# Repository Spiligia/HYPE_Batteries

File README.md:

**Boston University EC 463 & 464 Senior Design Project**

Members: Spencer Piligian, Ismaeel AlAlawi, Steven Wang, Yusheng Chen and Daniel Kao

## Welcome to Team 23: HYP Batteries! 

Our hybrid-chemistry battery pack design aims to fill niche market gap in high performance battery pack for small aircraft by combining two batteries with two different discharge characteristics. These two cell chemistries can achieve a variable-max discharge rate, allowing us to design a smaller battery pack while also fulfilling power requirements during the launch. This pack setup will help eGliders achieve a safe flight through the use of electric power and as a result, will minimize the risk of mechanical failure for our client’s conventional mechanical engines, whose vibration causes other parts of the aircraft to wear out and ultimately increases the chance of failure.

Link to google drive for more information / process development 

https://drive.google.com/drive/u/0/folders/0AN8LmBJzQ7HJUk9PVA

For member access please email: spiligia@bu.edu

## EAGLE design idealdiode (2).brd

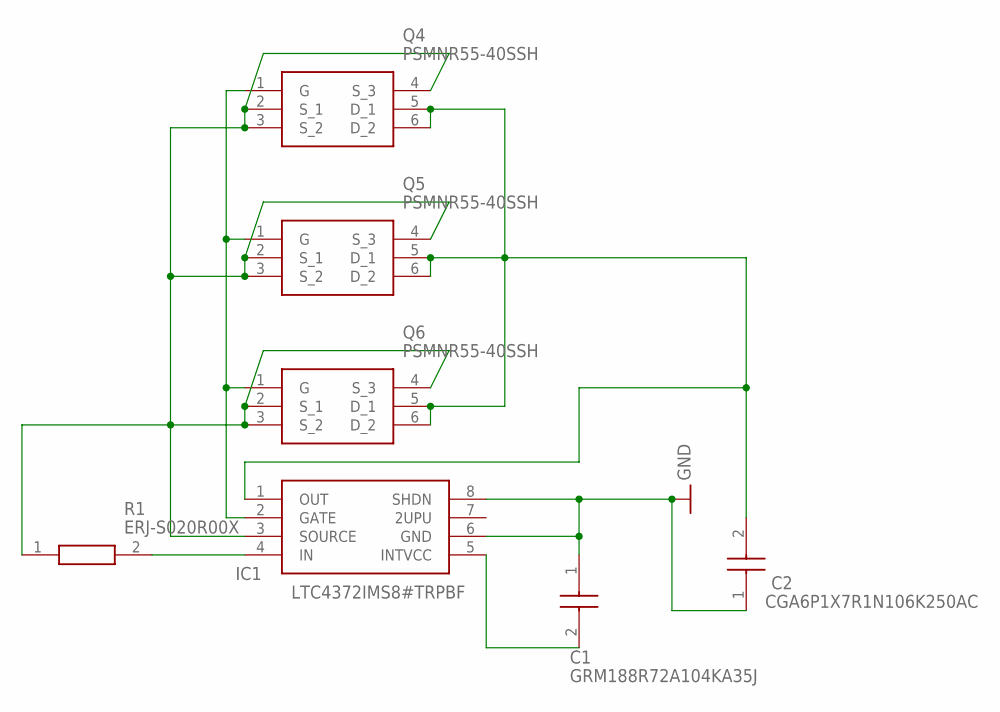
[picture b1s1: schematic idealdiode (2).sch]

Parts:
C1: GRM188R72A104KA35J; CAPC1608X90N
C2: CGA6P1X7R1N106K250AC; CAPC3225X280N
IC1: LTC4372IMS8#TRPBF; SOP65P490X110-8N
Q4, Q5, Q6: PSMNR55-40SSH; PSMNR5540SSH
R1: ERJ-S020R00X; ERJS02_U02_(0402)

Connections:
GND: C1.1, C2.1, IC1.6 (GND), IC1.8 (SHDN)
unnamed: IC1.2 (GATE), Q4.1 (G), Q5.1 (G), Q6.1 (G)
unnamed: IC1.3 (SOURCE), Q4.2 (S_1), Q4.3 (S_2), Q4.4 (S_3), Q5.2 (S_1), Q5.3 (S_2), Q5.4 (S_3), Q6.2 (S_1), Q6.3 (S_2), Q6.4 (S_3), R1.1
unnamed: C2.2, IC1.1 (OUT), Q4.5 (D_1), Q4.6 (D_2), Q5.5 (D_1), Q5.6 (D_2), Q6.5 (D_1), Q6.6 (D_2)
unnamed: C1.2, IC1.5 (INTVCC)
unnamed: IC1.4 (IN), R1.2

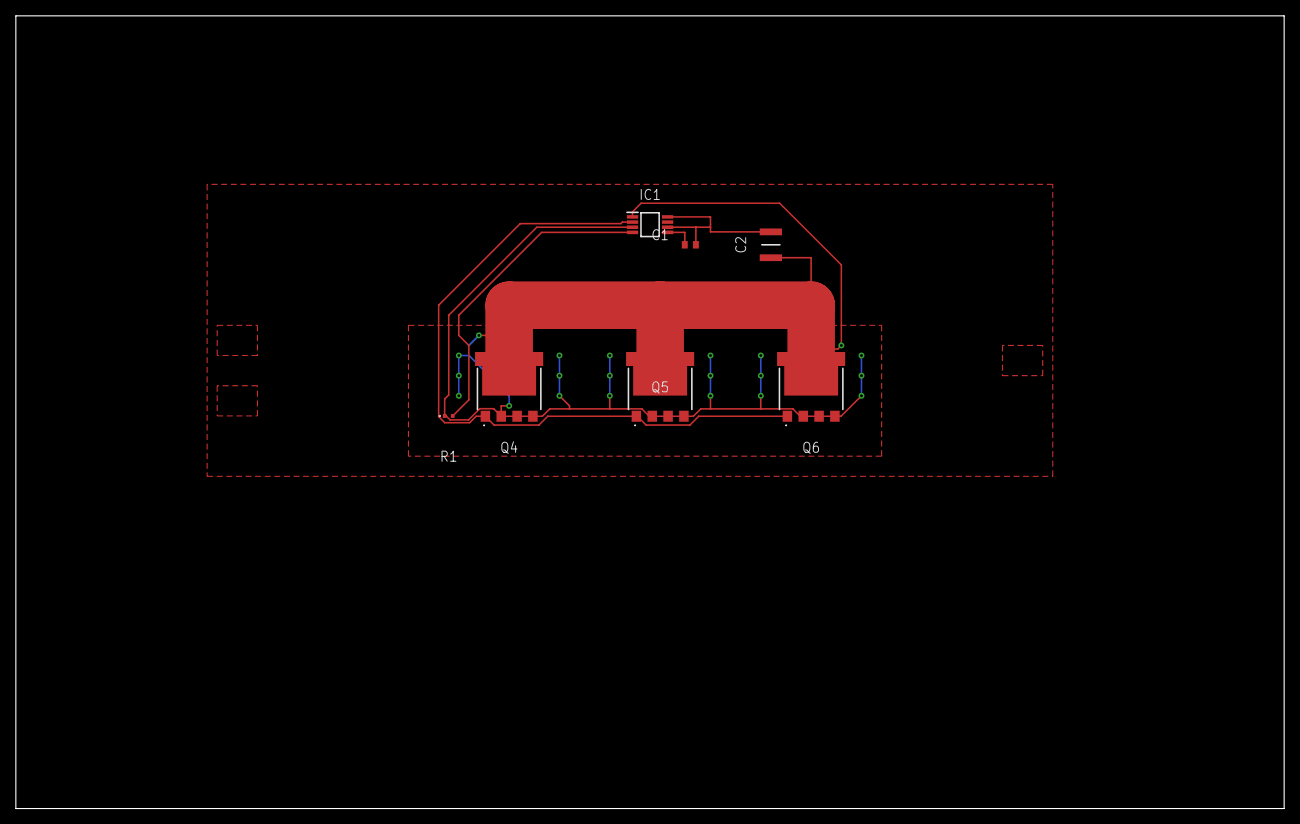
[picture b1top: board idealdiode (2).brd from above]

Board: 2 copper layers, 160.0 x 100.0 mm, 7 parts (0 on the bottom side), 6 nets.

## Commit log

2022-01-26 Code for temp control
    Using an arduino BLE
2022-01-26 udpate name
2022-01-26 .ino ext added
2022-01-27 updated some values for base arduino
    1023bit for non ble arduinos - may use megas
2022-02-01 output update
    set output text to serial monitor if over temp
2022-04-15 Renders of Thermistor cell boards
    - add grbr/ kicad files
2022-04-15 Create BatteryDisplay
    App for Battery Display
2022-04-15 Add files via upload
    Battery Display App
2022-04-16 Design files for thermistor daisy chain boards
    Done in KiCad verion 6. Full data for print GBR/Drill
2022-04-17 Create README_SOFTWARE.md
    added software readme
2022-04-17 Rename README.md to README_HARDWARE.md
    changed to hardware to distinguish both README files
2022-04-17 Create battery_testbench_v1.00.lisp
    Automated battery pack testbench using Lisp
2022-04-18 Ideal Diode Controller PCB
2022-04-18 Thermistor daisy board unzipped
    + read_me
2022-04-26 add files
2022-04-27 Updated heatmapimageprovider.cpp
    add additional json array variable and how the data will draw uonto the map
2022-04-29 Add files via upload
    naive testbench for motor current control
2022-04-29 Delete Directory
    File names contain spaces, causing failiure to pull needs to be re named
2022-04-29 update software readme
2022-04-29 pcis
2022-04-29 pics
    pics
2022-04-29 pics
2022-04-29 Delete 3D_Battery_holders directory
    pull issue
2022-04-30 Delete Prototype_Test directory
    Directory has space " prototype_test(space)" error pulling
